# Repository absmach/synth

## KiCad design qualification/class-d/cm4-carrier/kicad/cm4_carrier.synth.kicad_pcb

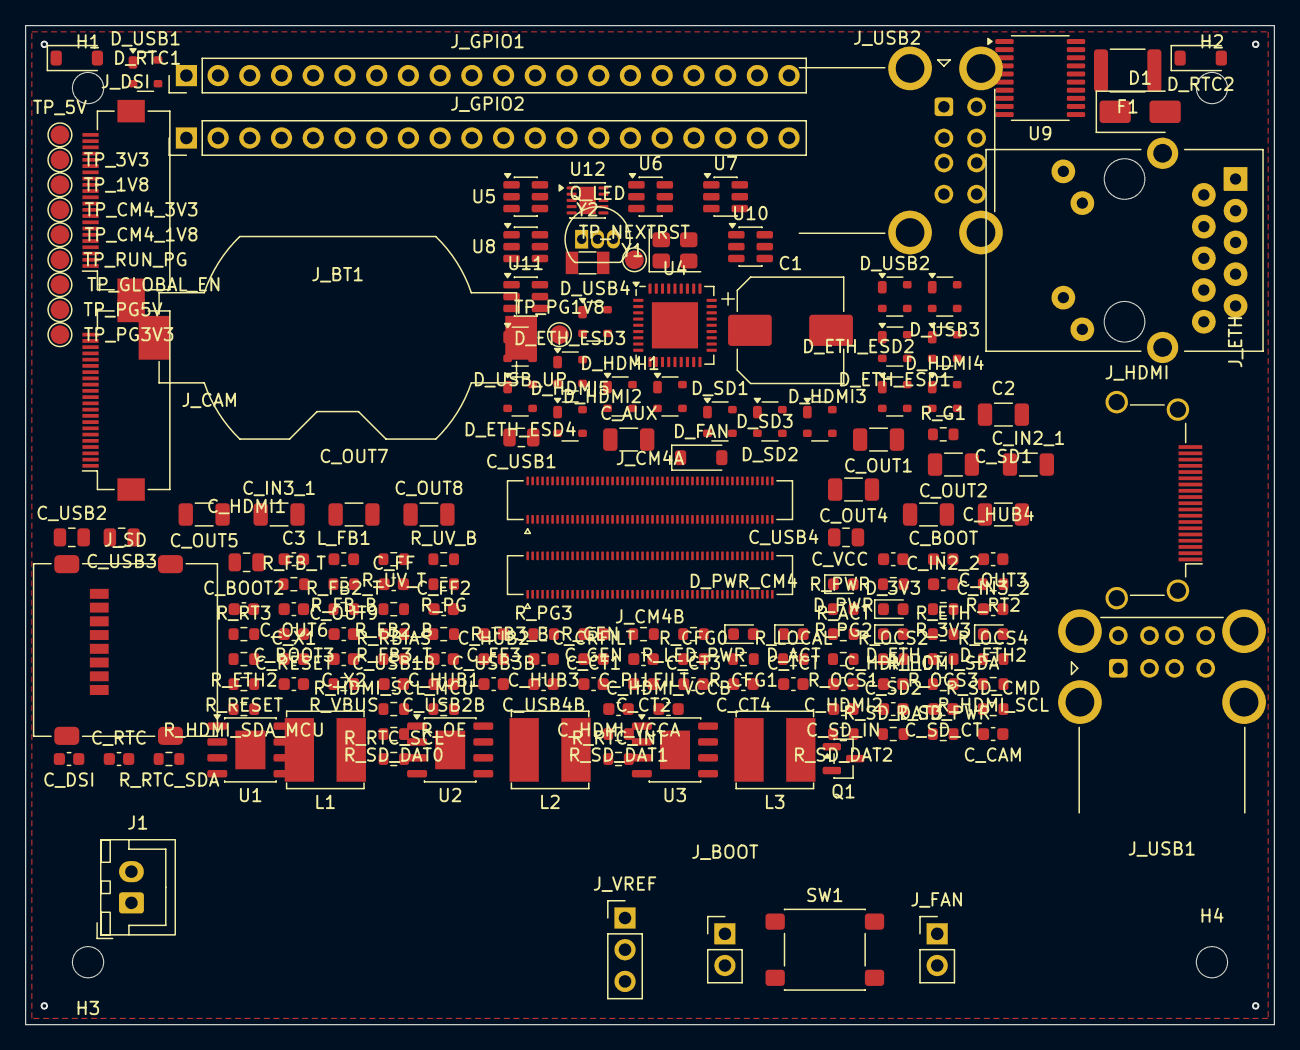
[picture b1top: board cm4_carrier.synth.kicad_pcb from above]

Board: 4 copper layers, 100.0 x 80.0 mm, 184 parts (0 on the bottom side), 158 nets, no tracks yet.

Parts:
C1: 47uF; CP_Elec_8x10
C2: 10uF; C_1206_3216Metric
C3: 220nF; C_0603_1608Metric
C_AUX: 10uF; C_1206_3216Metric
C_BOOT, C_BOOT2, C_BOOT3: 100nF; C_0603_1608Metric
C_CAM: 100nF; C_0603_1608Metric
C_CRFILT: 100nF; C_0603_1608Metric
C_CT1, C_CT2, C_CT3, C_CT4: 1nF; C_0603_1608Metric
C_DSI: 100nF; C_0603_1608Metric
C_FF, C_FF3: 100pF; C_0603_1608Metric
C_FF2: 56pF; C_0603_1608Metric
C_GEN: 100nF; C_0603_1608Metric
C_HDMI1: 1uF; C_0805_2012Metric
C_HDMI2: 100nF; C_0603_1608Metric
C_HDMI_CT: 1nF; C_0603_1608Metric
C_HDMI_VCCA: 100nF; C_0603_1608Metric
C_HDMI_VCCB: 100nF; C_0603_1608Metric
C_HUB1, C_HUB2, C_HUB3: 100nF; C_0603_1608Metric
C_HUB4: 10uF; C_1206_3216Metric
C_IN2_1, C_IN3_1: 10uF; C_1206_3216Metric
C_IN2_2, C_IN3_2: 220nF; C_0603_1608Metric
C_OUT1, C_OUT2, C_OUT4, C_OUT5, C_OUT7, C_OUT8: 22uF; C_1206_3216Metric
C_OUT3, C_OUT6, C_OUT9: 100nF; C_0603_1608Metric
C_PLLFILT: 100nF; C_0603_1608Metric
C_RESET: 1uF; C_0603_1608Metric
C_RTC: 100nF; C_0603_1608Metric
C_SD1: 10uF; C_1206_3216Metric
C_SD2: 100nF; C_0603_1608Metric
C_SD_CT: 1nF; C_0603_1608Metric
C_SD_IN: 100nF; C_0603_1608Metric
C_TCT: 100nF; C_0603_1608Metric
C_USB1, C_USB2, C_USB3, C_USB4: 1uF; C_0805_2012Metric
C_USB1B, C_USB2B, C_USB3B, C_USB4B: 100nF; C_0603_1608Metric
C_VCC: 1uF; C_0603_1608Metric
C_X1, C_X2: 18pF; C_0603_1608Metric
D1: SMAJ15A; D_SMA
D_3V3: 3V3; LED_0603_1608Metric
D_ACT: ACT; LED_0603_1608Metric
D_ETH: ETH_ACT; LED_0603_1608Metric
D_ETH2: ETH_SPD; LED_0603_1608Metric
D_ETH_ESD1, D_ETH_ESD2, D_ETH_ESD3, D_ETH_ESD4: TVS; SOT-143
D_FAN: FLYBACK; D_SOD-123
D_HDMI1, D_HDMI2, D_HDMI3, D_HDMI4, D_HDMI5: TVS; SOT-143
D_PWR: 5V; LED_0603_1608Metric
D_PWR_CM4: PWR; LED_0603_1608Metric
D_RTC1: 3V3; D_SOD-123
D_RTC2: BAT; D_SOD-123
D_SD1, D_SD2, D_SD3: TVS; SOT-143
D_USB1, D_USB2, D_USB3, D_USB4: TVS; SOT-143
D_USB_UP: TVS; SOT-143
F1: 2.6A_PTC; Fuse_1812_4532Metric
H1, H2, H3, H4: M2.5; MountingHole_2.5mm
J1: 12V_IN; JST_XH_B2B-XH-A_1x02_P2.50mm_Vertical
J_BOOT: nRPIBOOT; PinHeader_1x02_P2.54mm_Vertical
J_BT1: CR2032; BatteryHolder_Keystone_1058_1x2032
J_CAM: CSI0; Hirose_FH12-22S-0.5SH_1x22-1MP_P0.50mm_Horizontal
J_CM4A: CM4_A; Hirose_DF40C-100DS-0.4V_2x50_P0.4mm
J_CM4B: CM4_B; Hirose_DF40C-100DS-0.4V_2x50_P0.4mm
J_DSI: DSI0; Hirose_FH12-22S-0.5SH_1x22-1MP_P0.50mm_Horizontal
J_ETH: GbE; RJ45_UDE_RB1-125B8G1A
J_FAN: FAN; PinHeader_1x02_P2.54mm_Vertical
J_GPIO1: GPIO_ODD; PinHeader_1x20_P2.54mm_Vertical
J_GPIO2: GPIO_EVEN; PinHeader_1x20_P2.54mm_Vertical
J_HDMI: HDMI0; HDMI_A_Amphenol_10029449-x01xLF_Horizontal
J_SD: microSD; microSD_HC_Molex_47219-2001
J_USB1: USB1_2; USB_A_CUI_UJ2-ADH-TH_Horizontal_Stacked
J_USB2: USB3_4; USB_A_CUI_UJ2-ADH-TH_Horizontal_Stacked
J_VREF: VREF_SEL; PinHeader_1x03_P2.54mm_Vertical
L1, L2, L3: 6.8uH; L_Bourns_SRN6045TA
L_FB1: 600R; L_0603_1608Metric
Q1: DMP3098L; SOT-23
Q_LED: 2N7000; TO-92_Inline
R_3V3: 470; R_0603_1608Metric
R_ACT: 470; R_0603_1608Metric
R_CFG0, R_CFG1: 10k; R_0603_1608Metric
R_ETH, R_ETH2: 470; R_0603_1608Metric
R_FB2_B: 43.2k; R_0603_1608Metric
R_FB2_T, R_FB3_T: 100k; R_0603_1608Metric
R_FB3_B: 125k; R_0603_1608Metric
R_FB_B: 24.9k; R_0603_1608Metric
R_FB_T: 100k; R_0603_1608Metric
R_G1: 100k; R_0603_1608Metric
R_GEN: 100k; R_0603_1608Metric
R_HDMI_SCL: 2.2k; R_0603_1608Metric
R_HDMI_SCL_MCU: 2.2k; R_0603_1608Metric
R_HDMI_SDA: 2.2k; R_0603_1608Metric
R_HDMI_SDA_MCU: 2.2k; R_0603_1608Metric
R_LED_PWR: 470; R_0603_1608Metric
R_LOCAL: 10k; R_0603_1608Metric
R_OCS1, R_OCS2, R_OCS3, R_OCS4: 10k; R_0603_1608Metric
R_OE: 10k; R_0603_1608Metric
R_PG, R_PG2, R_PG3: 100k; R_0603_1608Metric
R_PWR: 470; R_0603_1608Metric
R_RBIAS: 12k; R_0603_1608Metric
R_RESET: 10k; R_0603_1608Metric
R_RT2, R_RT3: 33k; R_0603_1608Metric
R_RTC_INT: 10k; R_0603_1608Metric
R_RTC_SCL: 10k; R_0603_1608Metric
R_RTC_SDA: 10k; R_0603_1608Metric
R_SD_CMD: 10k; R_0603_1608Metric
R_SD_DAT0, R_SD_DAT1, R_SD_DAT2, R_SD_DAT3: 10k; R_0603_1608Metric
R_SD_PWR: 100k; R_0603_1608Metric
R_UV_B: 10k; R_0603_1608Metric
R_UV_T: 63.4k; R_0603_1608Metric
R_VBUS: 10k; R_0603_1608Metric
SW1: GLOBAL_EN; SW_SPST_PTS645Sx43SMTR92
TP_1V8: 1V8; TestPoint_Pad_D1.5mm
TP_3V3: 3V3; TestPoint_Pad_D1.5mm
TP_5V: 5V; TestPoint_Pad_D1.5mm
TP_CM4_1V8: CM4_1V8; TestPoint_Pad_D1.5mm
TP_CM4_3V3: CM4_3V3; TestPoint_Pad_D1.5mm
TP_GLOBAL_EN: GLOBAL_EN; TestPoint_Pad_D1.5mm
TP_NEXTRST: nEXTRST; TestPoint_Pad_D1.5mm
TP_PG1V8: PG_1V8; TestPoint_Pad_D1.5mm
TP_PG3V3: PG_3V3; TestPoint_Pad_D1.5mm
TP_PG5V: PG_5V; TestPoint_Pad_D1.5mm
TP_RUN_PG: RUN_PG; TestPoint_Pad_D1.5mm
U1: LMR33640; HSOP-8-1EP_3.9x4.9mm_P1.27mm_EP2.41x3.1mm
U2, U3: LMR38010; HSOP-8-1EP_3.9x4.9mm_P1.27mm_EP2.41x3.1mm
U4: USB2514B; QFN-36-1EP_6x6mm_P0.5mm_EP3.7x3.7mm
U5: USB1_PWR; SOT-23-6
U6: USB2_PWR; SOT-23-6
U7: USB3_PWR; SOT-23-6
U8: USB4_PWR; SOT-23-6
U9: TXS0108E; TSSOP-20_4.4x6.5mm_P0.65mm
U10: HDMI_5V; SOT-23-6
U11: SD_PWR; SOT-23-6
U12: PCF85063A; DFN-10-1EP_2.6x2.6mm_P0.5mm_EP1.3x2.2mm
Y1: 24MHz; Crystal_SMD_3225-4Pin_3.2x2.5mm
Y2: 32.768kHz; Crystal_SMD_3215-2Pin_3.2x1.5mm

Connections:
+1V8: C_OUT7.1, C_OUT8.1, C_OUT9.1, J_VREF.3, L3.2, R_FB3_T.1, R_PG3.1, TP_1V8.1
+3V3: C_CAM.1, C_DSI.1, C_HDMI_VCCA.1, C_HUB1.1, C_HUB2.1, C_HUB3.1, C_HUB4.1, C_OUT4.1, C_OUT5.1, C_OUT6.1, C_SD_IN.1, D_ETH_ESD1.4, D_ETH_ESD2.4, D_ETH_ESD3.4, D_ETH_ESD4.4, D_HDMI1.4, D_HDMI2.4, D_HDMI3.4, D_HDMI4.4, D_RTC1.2, D_USB_UP.4, J_CAM.18, J_CAM.22, J_DSI.17, J_DSI.22, J_GPIO1.1, J_GPIO1.9, J_VREF.1, L2.2, R_3V3.1, R_ACT.1, R_ETH.1, R_ETH2.1, R_FB2_T.1, R_GEN.1, R_HDMI_SCL_MCU.1, R_HDMI_SDA_MCU.1, R_LED_PWR.1, R_OCS1.1, R_OCS2.1, R_OCS3.1, R_OCS4.1, R_OE.1, R_PG2.1, R_RESET.1, R_SD_PWR.1, R_VBUS.1, TP_3V3.1, U4.5, U4.10, U4.15, U4.23, U4.29, U4.36, U9.2, U10.3, U11.1
+5V: C_HDMI_VCCB.1, C_OUT1.1, C_OUT2.1, C_OUT3.1, D_FAN.1, D_HDMI5.4, J_CM4A.77, J_CM4A.79, J_CM4A.81, J_CM4A.83, J_CM4A.85, J_CM4A.87, J_FAN.1, J_GPIO2.1, J_GPIO2.2, L1.2, L_FB1.1, R_FB_T.1, R_PG.1, R_PWR.1, TP_5V.1, U5.1, U6.1, U7.1, U8.1, U9.19, U10.1
+5V_AUX: C_AUX.1, C_IN2_1.1, C_IN2_2.1, C_IN3_1.1, C_IN3_2.1, L_FB1.2, U2.3, U3.3
BOOT_1V8: C_BOOT3.1, U3.7
BOOT_3V3: C_BOOT2.1, U2.7
BOOT_5V: C_BOOT.1, U1.7
CAM_CK_N: J_CAM.8, J_CM4B.40
CAM_CK_P: J_CAM.9, J_CM4B.42
CAM_D0_N: J_CAM.2, J_CM4B.28
CAM_D0_P: J_CAM.3, J_CM4B.30
CAM_D1_N: J_CAM.5, J_CM4B.34
CAM_D1_P: J_CAM.6, J_CM4B.36
CAM_GPIO: J_CAM.17, J_CM4A.97
CM4_1V8: J_CM4A.88, J_CM4A.90, TP_CM4_1V8.1
CM4_3V3: J_CM4A.84, J_CM4A.86, TP_CM4_3V3.1
DSI_CK_N: J_CM4B.69, J_DSI.8
DSI_CK_P: J_CM4B.71, J_DSI.9
DSI_D0_N: J_CM4B.57, J_DSI.2
DSI_D0_P: J_CM4B.59, J_DSI.3
DSI_D1_N: J_CM4B.63, J_DSI.5
DSI_D1_P: J_CM4B.65, J_DSI.6
ETH0_N: D_ETH_ESD1.3, J_CM4A.10, J_ETH.R3
ETH0_P: D_ETH_ESD1.2, J_CM4A.12, J_ETH.R2
ETH1_N: D_ETH_ESD2.3, J_CM4A.6, J_ETH.R5
ETH1_P: D_ETH_ESD2.2, J_CM4A.4, J_ETH.R4
ETH2_N: D_ETH_ESD3.3, J_CM4A.9, J_ETH.R7
ETH2_P: D_ETH_ESD3.2, J_CM4A.11, J_ETH.R6
ETH3_N: D_ETH_ESD4.3, J_CM4A.5, J_ETH.R9
ETH3_P: D_ETH_ESD4.2, J_CM4A.3, J_ETH.R8
ETH_LED_ACT: D_ETH.1, J_CM4A.15
ETH_LED_SPD: D_ETH2.1, J_CM4A.17
ETH_TCT: C_TCT.1, J_ETH.R1
FB_1V8: C_FF3.1, R_FB3_B.1, R_FB3_T.2, U3.5
FB_3V3: C_FF2.1, R_FB2_B.1, R_FB2_T.2, U2.5
FB_5V: C_FF.1, R_FB_B.1, R_FB_T.2, U1.5
GLOBAL_EN: C_GEN.1, J_CM4A.99, R_GEN.2, SW1.1, TP_GLOBAL_EN.1
GND: C1.2, C2.2, C3.2, C_AUX.2, C_CAM.2, C_CRFILT.2, C_CT1.2, C_CT2.2, C_CT3.2, C_CT4.2, C_DSI.2, C_GEN.2, C_HDMI1.2, C_HDMI2.2, C_HDMI_CT.2, C_HDMI_VCCA.2, C_HDMI_VCCB.2, C_HUB1.2, C_HUB2.2, C_HUB3.2, C_HUB4.2, C_IN2_1.2, C_IN2_2.2, C_IN3_1.2, C_IN3_2.2, C_OUT1.2, C_OUT2.2, C_OUT3.2, C_OUT4.2, C_OUT5.2, C_OUT6.2, C_OUT7.2, C_OUT8.2, C_OUT9.2, C_PLLFILT.2, C_RESET.2, C_RTC.2, C_SD1.2, C_SD2.2, C_SD_CT.2, C_SD_IN.2, C_TCT.2, C_USB1.2, C_USB1B.2, C_USB2.2, C_USB2B.2, C_USB3.2, C_USB3B.2, C_USB4.2, C_USB4B.2, C_VCC.2, C_X1.2, C_X2.2, D1.2, D_3V3.1, D_ETH_ESD1.1, D_ETH_ESD2.1, D_ETH_ESD3.1, D_ETH_ESD4.1, D_FAN.2, D_HDMI1.1, D_HDMI2.1, D_HDMI3.1, D_HDMI4.1, D_HDMI5.1, D_PWR.1, D_SD1.1, D_SD2.1, D_SD3.1, D_USB1.1, D_USB2.1, D_USB3.1, D_USB4.1, D_USB_UP.1, J1.2, J_BOOT.2, J_BT1.2, J_CAM.1, J_CAM.4, J_CAM.7, J_CAM.10, J_CAM.13, J_CAM.16, J_CAM.19, J_CAM.MP, J_CM4A.1, J_CM4A.2, J_CM4A.7, J_CM4A.8, J_CM4A.13, J_CM4A.14, J_CM4A.22, J_CM4A.23, J_CM4A.32, J_CM4A.33, J_CM4A.42, J_CM4A.43, J_CM4A.52, J_CM4A.53, J_CM4A.59, J_CM4A.60, J_CM4A.65, J_CM4A.66, J_CM4A.71, J_CM4A.74, J_CM4A.98, J_CM4B.1, J_CM4B.7, J_CM4B.8, J_CM4B.13, J_CM4B.14, J_CM4B.19, J_CM4B.20, J_CM4B.25, J_CM4B.26, J_CM4B.31, J_CM4B.32, J_CM4B.37, J_CM4B.38, J_CM4B.44, J_CM4B.50, J_CM4B.55, J_CM4B.56, J_CM4B.61, J_CM4B.62, J_CM4B.67, J_CM4B.68, J_CM4B.73, J_CM4B.74, J_CM4B.79, J_CM4B.80, J_CM4B.85, J_CM4B.86, J_CM4B.91, J_CM4B.92, J_CM4B.97, J_CM4B.98, J_DSI.1, J_DSI.4, J_DSI.7, J_DSI.10, J_DSI.13, J_DSI.16, J_DSI.19, J_DSI.MP, J_ETH.R10, J_ETH.SH, J_FAN.2, J_GPIO1.5, J_GPIO1.13, J_GPIO1.20, J_GPIO2.3, J_GPIO2.7, J_GPIO2.10, J_GPIO2.15, J_GPIO2.17, J_HDMI.2, J_HDMI.5, J_HDMI.8, J_HDMI.11, J_HDMI.17, J_HDMI.SH, J_SD.6, J_SD.SH, J_USB1.4, J_USB1.8, J_USB1.SH, J_USB2.4, J_USB2.8, J_USB2.SH, Q_LED.1, R_3V3.2, R_CFG0.2, R_CFG1.2, R_FB2_B.2, R_FB3_B.2, R_FB_B.2, R_LOCAL.2, R_PWR.2, R_RBIAS.2, R_RT2.2, R_RT3.2, R_UV_B.2, SW1.2, U1.1, U1.9, U2.1, U2.9, U3.1, U3.9, U4.37, U5.2, U6.2, U7.2, U8.2, U9.11, U10.2, U11.2, U12.5, U12.11, Y1.2, Y1.4
GPIO2: J_CM4A.58, J_GPIO1.2
GPIO3: J_CM4A.56, J_GPIO1.3
GPIO4: J_CM4A.54, J_GPIO1.4
GPIO5: J_CM4A.34, J_GPIO1.15
GPIO6: J_CM4A.30, J_GPIO1.16
GPIO7: J_CM4A.37, J_GPIO2.13
GPIO8: J_CM4A.39, J_GPIO2.12
GPIO9: J_CM4A.40, J_GPIO1.11
GPIO10: J_CM4A.44, J_GPIO1.10
GPIO11: J_CM4A.38, J_GPIO1.12
GPIO12: J_CM4A.31, J_GPIO2.16
GPIO13: J_CM4A.28, J_GPIO1.17
GPIO14: J_CM4A.55, J_GPIO2.4
GPIO15: J_CM4A.51, J_GPIO2.5
GPIO16: J_CM4A.29, J_GPIO2.18
GPIO17: J_CM4A.50, J_GPIO1.6
GPIO18: J_CM4A.49, J_GPIO2.6
GPIO19: J_CM4A.26, J_GPIO1.18
GPIO20: J_CM4A.27, J_GPIO2.19
GPIO21: J_CM4A.25, J_GPIO2.20
GPIO22: J_CM4A.46, J_GPIO1.8
GPIO23: J_CM4A.47, J_GPIO2.8
GPIO24: J_CM4A.45, J_GPIO2.9
GPIO25: J_CM4A.41, J_GPIO2.11
GPIO26: J_CM4A.24, J_GPIO1.19, R_RTC_INT.2, U12.4
GPIO27: J_CM4A.48, J_GPIO1.7
GPIO_VREF: J_CM4A.78, J_VREF.2
HDMI_5V: C_HDMI1.1, C_HDMI2.1, J_HDMI.18, U10.6
HDMI_CEC: J_CM4B.51, J_HDMI.13
HDMI_CK_N: D_HDMI4.3, J_CM4B.90, J_HDMI.12
HDMI_CK_P: D_HDMI4.2, J_CM4B.88, J_HDMI.10
HDMI_CT: C_HDMI_CT.1, U10.4
HDMI_D0_N: D_HDMI3.3, J_CM4B.84, J_HDMI.9
HDMI_D0_P: D_HDMI3.2, J_CM4B.82, J_HDMI.7
HDMI_D1_N: D_HDMI2.3, J_CM4B.78, J_HDMI.6
HDMI_D1_P: D_HDMI2.2, J_CM4B.76, J_HDMI.4
HDMI_D2_N: D_HDMI1.3, J_CM4B.72, J_HDMI.3
HDMI_D2_P: D_HDMI1.2, J_CM4B.70, J_HDMI.1
HDMI_HPD: J_CM4B.53, J_HDMI.19
HDMI_OE: R_OE.2, U9.10
HDMI_SCL_CONN: D_HDMI5.3, J_HDMI.15, R_HDMI_SCL.1, U9.18
HDMI_SCL_MCU: J_CM4B.100, R_HDMI_SCL_MCU.2, U9.3
HDMI_SDA_CONN: D_HDMI5.2, J_HDMI.16, R_HDMI_SDA.1, U9.20
HDMI_SDA_MCU: J_CM4B.99, R_HDMI_SDA_MCU.2, U9.1
HUB_CFG0: R_CFG0.1, U4.24
HUB_CFG1: R_CFG1.1, U4.25
HUB_CRFILT: C_CRFILT.1, U4.14
HUB_LOCAL: R_LOCAL.1, U4.28
HUB_OCS1: R_OCS1.2, U4.13
HUB_OCS2: R_OCS2.2, U4.17
HUB_OCS3: R_OCS3.2, U4.19
HUB_OCS4: R_OCS4.2, U4.21
HUB_PLLFILT: C_PLLFILT.1, U4.34
HUB_RBIAS: R_RBIAS.1, U4.35
HUB_RESET: C_RESET.1, R_RESET.2, U4.26
HUB_VBUS_DET: R_VBUS.2, U4.27
HUB_XTAL1: C_X1.1, U4.33, Y1.1
HUB_XTAL2: C_X2.1, U4.32, Y1.3
ID_SC: J_CM4A.35, J_GPIO2.14
ID_SD: J_CM4A.36, J_GPIO1.14
LED_ACT_A: D_ACT.2, R_ACT.2
LED_ETH2_A: D_ETH2.2, R_ETH2.2
LED_ETH_A: D_ETH.2, R_ETH.2
LED_PWR_CM4: D_PWR_CM4.1, Q_LED.3
LED_PWR_CM4_A: D_PWR_CM4.2, R_LED_PWR.2
NEXTRST: J_CM4A.100, TP_NEXTRST.1
NRPIBOOT: J_BOOT.1, J_CM4A.93
PG_1V8: R_PG3.2, TP_PG1V8.1, U3.6
PG_3V3: R_PG2.2, TP_PG3V3.1, U2.6, U3.2
PG_5V: R_PG.2, TP_PG5V.1, U1.4, U2.2
PI_LED_ACT: D_ACT.1, J_CM4A.21
PI_LED_NPWR: J_CM4A.95, Q_LED.2
RTC_BAT: D_RTC2.2, J_BT1.1
RTC_OSC1: U12.1, Y2.1
RTC_OSC2: U12.2, Y2.2
RTC_VDD: C_RTC.1, D_RTC1.1, D_RTC2.1, R_RTC_INT.1, R_RTC_SCL.1, R_RTC_SDA.1, U12.3, U12.10
RT_1V8: R_RT3.1, U3.4
RT_3V3: R_RT2.1, U2.4
RUN_PG: J_CM4A.92, TP_RUN_PG.1
SCL0: J_CAM.20, J_CM4A.80, J_DSI.20, R_RTC_SCL.2, U12.7
SDA0: J_CAM.21, J_CM4A.82, J_DSI.21, R_RTC_SDA.2, U12.6
SD_CLK: D_SD1.2, J_CM4A.57, J_SD.5
SD_CMD: D_SD1.3, J_CM4A.62, J_SD.3, R_SD_CMD.2
SD_CT: C_SD_CT.1, U11.4
SD_DAT0: D_SD2.2, J_CM4A.63, J_SD.7, R_SD_DAT0.2
SD_DAT1: D_SD2.3, J_CM4A.67, J_SD.8, R_SD_DAT1.2
SD_DAT2: D_SD3.2, J_CM4A.69, J_SD.1, R_SD_DAT2.2
SD_DAT3: D_SD3.3, J_CM4A.61, J_SD.2, R_SD_DAT3.2
SD_PWR_ON: J_CM4A.75, R_SD_PWR.2, U11.3
SD_VDD: C_SD1.1, C_SD2.1, D_SD1.4, D_SD2.4, D_SD3.4, J_SD.4, R_SD_CMD.1, R_SD_DAT0.1, R_SD_DAT1.1, R_SD_DAT2.1, R_SD_DAT3.1, U11.6
SW_1V8: C_BOOT3.2, L3.1, U3.8
SW_3V3: C_BOOT2.2, L2.1, U2.8
SW_5V: C_BOOT.2, L1.1, U1.8
USB1_N: D_USB1.3, J_USB1.2, U4.1
USB1_P: D_USB1.2, J_USB1.3, U4.2
USB2_N: D_USB2.3, J_USB1.6, U4.3
USB2_P: D_USB2.2, J_USB1.7, U4.4
USB3_N: D_USB3.3, J_USB2.2, U4.6
USB3_P: D_USB3.2, J_USB2.3, U4.7
USB4_N: D_USB4.3, J_USB2.6, U4.8
USB4_P: D_USB4.2, J_USB2.7, U4.9
USB_CT1: C_CT1.1, U5.4
USB_CT2: C_CT2.1, U6.4
USB_CT3: C_CT3.1, U7.4
USB_CT4: C_CT4.1, U8.4
USB_ON1: U4.12, U5.3
USB_ON2: U4.16, U6.3
USB_ON3: U4.18, U7.3
USB_ON4: U4.20, U8.3
USB_UP_N: D_USB_UP.3, J_CM4B.3, U4.30
USB_UP_P: D_USB_UP.2, J_CM4B.5, U4.31
USB_VBUS1: C_USB1.1, C_USB1B.1, D_USB1.4, J_USB1.1, U5.6
USB_VBUS2: C_USB2.1, C_USB2B.1, D_USB2.4, J_USB1.5, U6.6
USB_VBUS3: C_USB3.1, C_USB3B.1, D_USB3.4, J_USB2.1, U7.6
USB_VBUS4: C_USB4.1, C_USB4B.1, D_USB4.4, J_USB2.5, U8.6
VCC_5V: C_VCC.1, U1.6
VIN_12V: F1.1, J1.1
VIN_FUSED: F1.2, Q1.2
VIN_GATE: Q1.1, R_G1.2
VIN_PROT: C1.1, C2.1, C3.1, D1.1, Q1.3, R_G1.1, R_UV_T.1, U1.2

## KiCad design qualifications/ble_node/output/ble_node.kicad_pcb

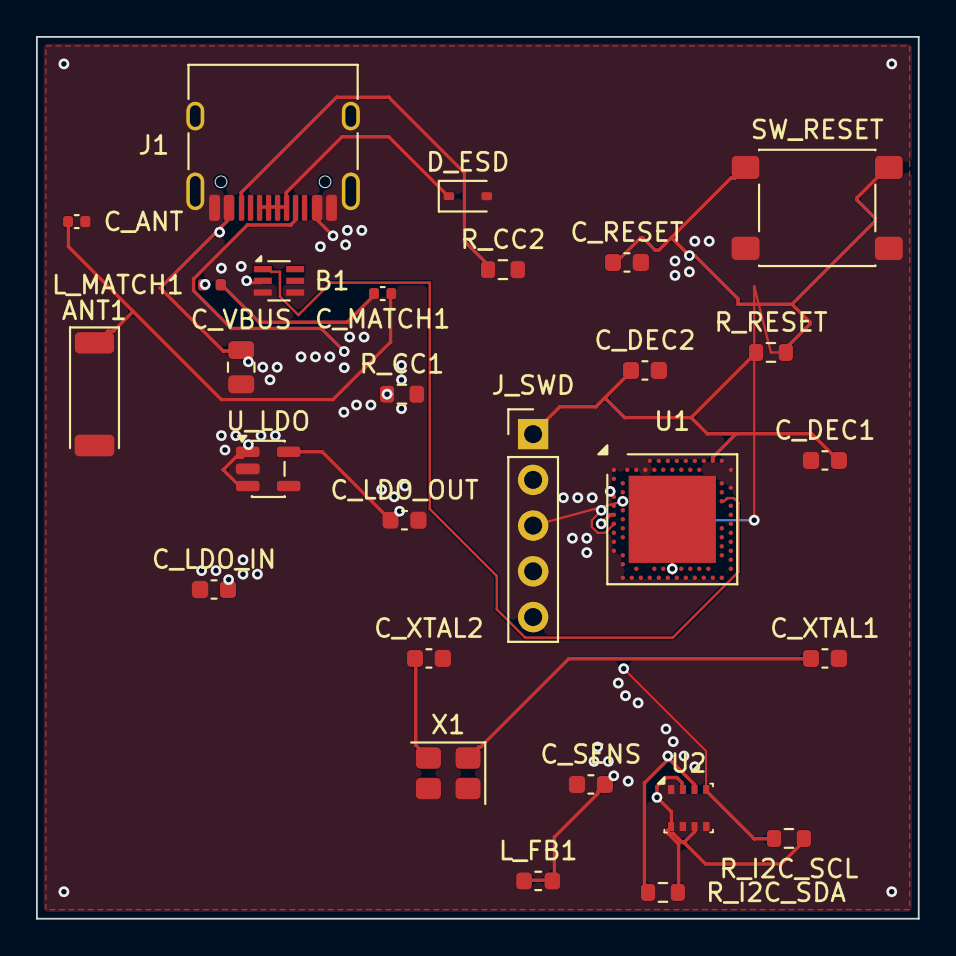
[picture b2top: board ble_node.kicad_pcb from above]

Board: 4 copper layers, 49.0 x 49.0 mm, 28 parts (0 on the bottom side), 17 nets.

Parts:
ANT1: 2.4GHz Chip Ant; Johanson_2450AT43F0100
B1: 2.4GHz Balun; Balun_Johanson_0896BM15A0001
C_ANT: 1.0pF; C_0402_1005Metric
C_DEC1, C_DEC2: 100nF; C_0603_1608Metric
C_LDO_IN: 1uF; C_0603_1608Metric
C_LDO_OUT: 1uF; C_0603_1608Metric
C_MATCH1: 1.0pF; C_0402_1005Metric
C_RESET: 100nF; C_0603_1608Metric
C_SENS: 100nF; C_0603_1608Metric
C_VBUS: 10uF; C_0805_2012Metric
C_XTAL1, C_XTAL2: 12pF; C_0603_1608Metric
D_ESD: (no value); D_SOD-323
J1: TYPE-C-31-M-12; USB_C_Receptacle_HRO_TYPE-C-31-M-12
J_SWD: SWD Header; PinHeader_1x05_P2.54mm_Vertical
L_FB1: (no value); L_0603_1608Metric
L_MATCH1: 3.9nH; L_0402_1005Metric
R_CC1, R_CC2: 5.1k; R_0603_1608Metric
R_I2C_SCL, R_I2C_SDA: 4.7k; R_0603_1608Metric
R_RESET: 10k; R_0603_1608Metric
SW_RESET: (no value); SW_SPST_PTS645Sx43SMTR92
U1: nRF52840-QIAA; Nordic_AQFN-73-1EP_7x7mm_P0.5mm
U2: BME680; Bosch_LGA-8_2.5x2.5mm_P0.65mm_ClockwisePinNumbering
U_LDO: LP5907-3.3; SOT-23-5
X1: 32 MHz; Crystal_SMD_3225-4Pin_3.2x2.5mm

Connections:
+3V3: C_DEC1.1, C_DEC2.1, C_LDO_OUT.1, C_SENS.1, J_SWD.1, L_FB1.1, L_FB1.2, R_I2C_SCL.2, R_I2C_SDA.2, R_RESET.1, U1.A22, U2.2, U2.6, U2.8, U_LDO.5
ANT_FEED: B1.1, U1.H23
GND: ANT1.2, B1.3, B1.4, C_ANT.2, C_DEC1.2, C_DEC2.2, C_LDO_IN.2, C_LDO_OUT.2, C_RESET.2, C_SENS.2, C_VBUS.2, C_XTAL1.2, C_XTAL2.2, D_ESD.2, J1.A1, J1.A12, J1.B1, J1.B12, J1.SH, J_SWD.4, R_CC1.2, R_CC2.2, SW_RESET.2, U1.B7, U2.1, U2.5, U2.7, U_LDO.2
net_0: C_LDO_IN.1, C_VBUS.1, J1.A4, J1.A9, J1.B4, J1.B9, U_LDO.1, U_LDO.3
net_3: J1.A5, R_CC1.1
net_4: J1.B5, R_CC2.1
net_5: D_ESD.1, J1.A6, J1.A7, J1.B6, J1.B7
net_6: C_RESET.1, J_SWD.5, R_RESET.2, SW_RESET.1, U1.AC13
net_7: C_XTAL1.1, X1.1
net_8: C_XTAL2.1, X1.2
net_9: B1.2, L_MATCH1.1
net_10: C_MATCH1.1, L_MATCH1.2
net_11: ANT1.1, C_ANT.1, C_MATCH1.2
net_12: R_I2C_SDA.1, U1.L1, U2.3
net_13: R_I2C_SCL.1, U1.N1, U2.4
net_14: J_SWD.2, U1.G1
net_15: J_SWD.3, U1.H2

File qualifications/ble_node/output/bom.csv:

refdes,value,kind,description,kicad_symbol,kicad_footprint,lcsc_pn,mpn
ANT1,2.4GHz Chip Ant,antenna,"Ceramic chip antenna, 2.4 GHz, 1 dBi, SMD",Device:Antenna_Chip,RF_Antenna:Johanson_2450AT43F0100,C17192881,2450AT43F0100E
B1,2.4GHz Balun,filter,"2.4 GHz balun + matching network, integrated SMD",RF_Module:balun_2g4,RF_Converter:Balun_Johanson_0896BM15A0001,,2450BL15B100
C_ANT,1.0pF,capacitor,"Generic 0402 MLCC, X7R/X5R, any value",Device:C,Capacitor_SMD:C_0402_1005Metric,,
C_DEC1,100nF,capacitor,"Generic 0603 MLCC, X7R/X5R, any value",Device:C,Capacitor_SMD:C_0603_1608Metric,,
C_DEC2,100nF,capacitor,"Generic 0603 MLCC, X7R/X5R, any value",Device:C,Capacitor_SMD:C_0603_1608Metric,,
C_LDO_IN,1uF,capacitor,"Generic 0603 MLCC, X7R/X5R, any value",Device:C,Capacitor_SMD:C_0603_1608Metric,,
C_LDO_OUT,1uF,capacitor,"Generic 0603 MLCC, X7R/X5R, any value",Device:C,Capacitor_SMD:C_0603_1608Metric,,
C_MATCH1,1.0pF,capacitor,"Generic 0402 MLCC, X7R/X5R, any value",Device:C,Capacitor_SMD:C_0402_1005Metric,,
C_RESET,100nF,capacitor,"Generic 0603 MLCC, X7R/X5R, any value",Device:C,Capacitor_SMD:C_0603_1608Metric,,
C_SENS,100nF,capacitor,"Generic 0603 MLCC, X7R/X5R, any value",Device:C,Capacitor_SMD:C_0603_1608Metric,,
C_VBUS,10uF,capacitor,"Generic 0805 MLCC, X7R/X5R, any value",Device:C,Capacitor_SMD:C_0805_2012Metric,,
C_XTAL1,12pF,capacitor,"Generic 0603 MLCC, X7R/X5R, any value",Device:C,Capacitor_SMD:C_0603_1608Metric,,
C_XTAL2,12pF,capacitor,"Generic 0603 MLCC, X7R/X5R, any value",Device:C,Capacitor_SMD:C_0603_1608Metric,,
D_ESD,(no value),diode,"USB-line ESD protection (TVS diode array), bidirectional",Device:D_TVS,Diode_SMD:D_SOD-323,,
J1,TYPE-C-31-M-12,connector,"USB-C receptacle, 24-pin SMD. Modelled here with primary and mirrored power/ground/data pins for full pad coverage.",Connector:USB_C_Receptacle,Connector_USB:USB_C_Receptacle_HRO_TYPE-C-31-M-12,C165948,TYPE-C-31-M-12
J_SWD,SWD Header,connector,"1x5 through-hole pin header, 2.54 mm pitch (SWD); datasheet_url is the product page of the Harwin M20 series, no manufacturer PDF link was verifiable",Connector_Generic:Conn_01x05,Connector_PinHeader_2.54mm:PinHeader_1x05_P2.54mm_Vertical,,
L_FB1,(no value),inductor,"0603 ferrite bead, 600Ω @ 100MHz — EMI suppression",Device:Ferrite_Bead,Inductor_SMD:L_0603_1608Metric,,
L_MATCH1,3.9nH,inductor,"Generic 0402 wirewound inductor, any value",Device:L,Inductor_SMD:L_0402_1005Metric,,
R_CC1,5.1k,resistor,"Generic 0603 thick-film resistor, any value",Device:R_US,Resistor_SMD:R_0603_1608Metric,,
R_CC2,5.1k,resistor,"Generic 0603 thick-film resistor, any value",Device:R_US,Resistor_SMD:R_0603_1608Metric,,
R_I2C_SCL,4.7k,resistor,"Generic 0603 thick-film resistor, any value",Device:R_US,Resistor_SMD:R_0603_1608Metric,,
R_I2C_SDA,4.7k,resistor,"Generic 0603 thick-film resistor, any value",Device:R_US,Resistor_SMD:R_0603_1608Metric,,
R_RESET,10k,resistor,"Generic 0603 thick-film resistor, any value",Device:R_US,Resistor_SMD:R_0603_1608Metric,,
SW_RESET,(no value),switch,Generic SPST tactile button,Switch:SW_Push,Button_Switch_SMD:SW_SPST_PTS645Sx43SMTR92,,
U1,nRF52840-QIAA,mcu,"Nordic nRF52840 ARM Cortex-M4F with BLE 5, I2C-capable GPIO naming",RF_Module:NRF52840-QIAA,Package_DFN_QFN:Nordic_AQFN-73-1EP_7x7mm_P0.5mm,C190794,NRF52840-QIAA-R
U2,BME680,sensor,"Bosch BME680 environmental sensor: T/RH/P/VOC, I²C",Sensor:BME680,Package_LGA:Bosch_LGA-8_2.5x2.5mm_P0.65mm_ClockwisePinNumbering,,
U_LDO,LP5907-3.3,regulator,"TI LP5907 3.3V low-noise LDO, 250mA, SOT-23-5",Regulator_Linear:LP5907MFX-3.3,Package_TO_SOT_SMD:SOT-23-5,C83437,LP5907MFX-3.3
X1,32 MHz,crystal,"Generic quartz crystal, 2-pin SMD",Device:Crystal,Crystal:Crystal_SMD_3225-4Pin_3.2x2.5mm,,

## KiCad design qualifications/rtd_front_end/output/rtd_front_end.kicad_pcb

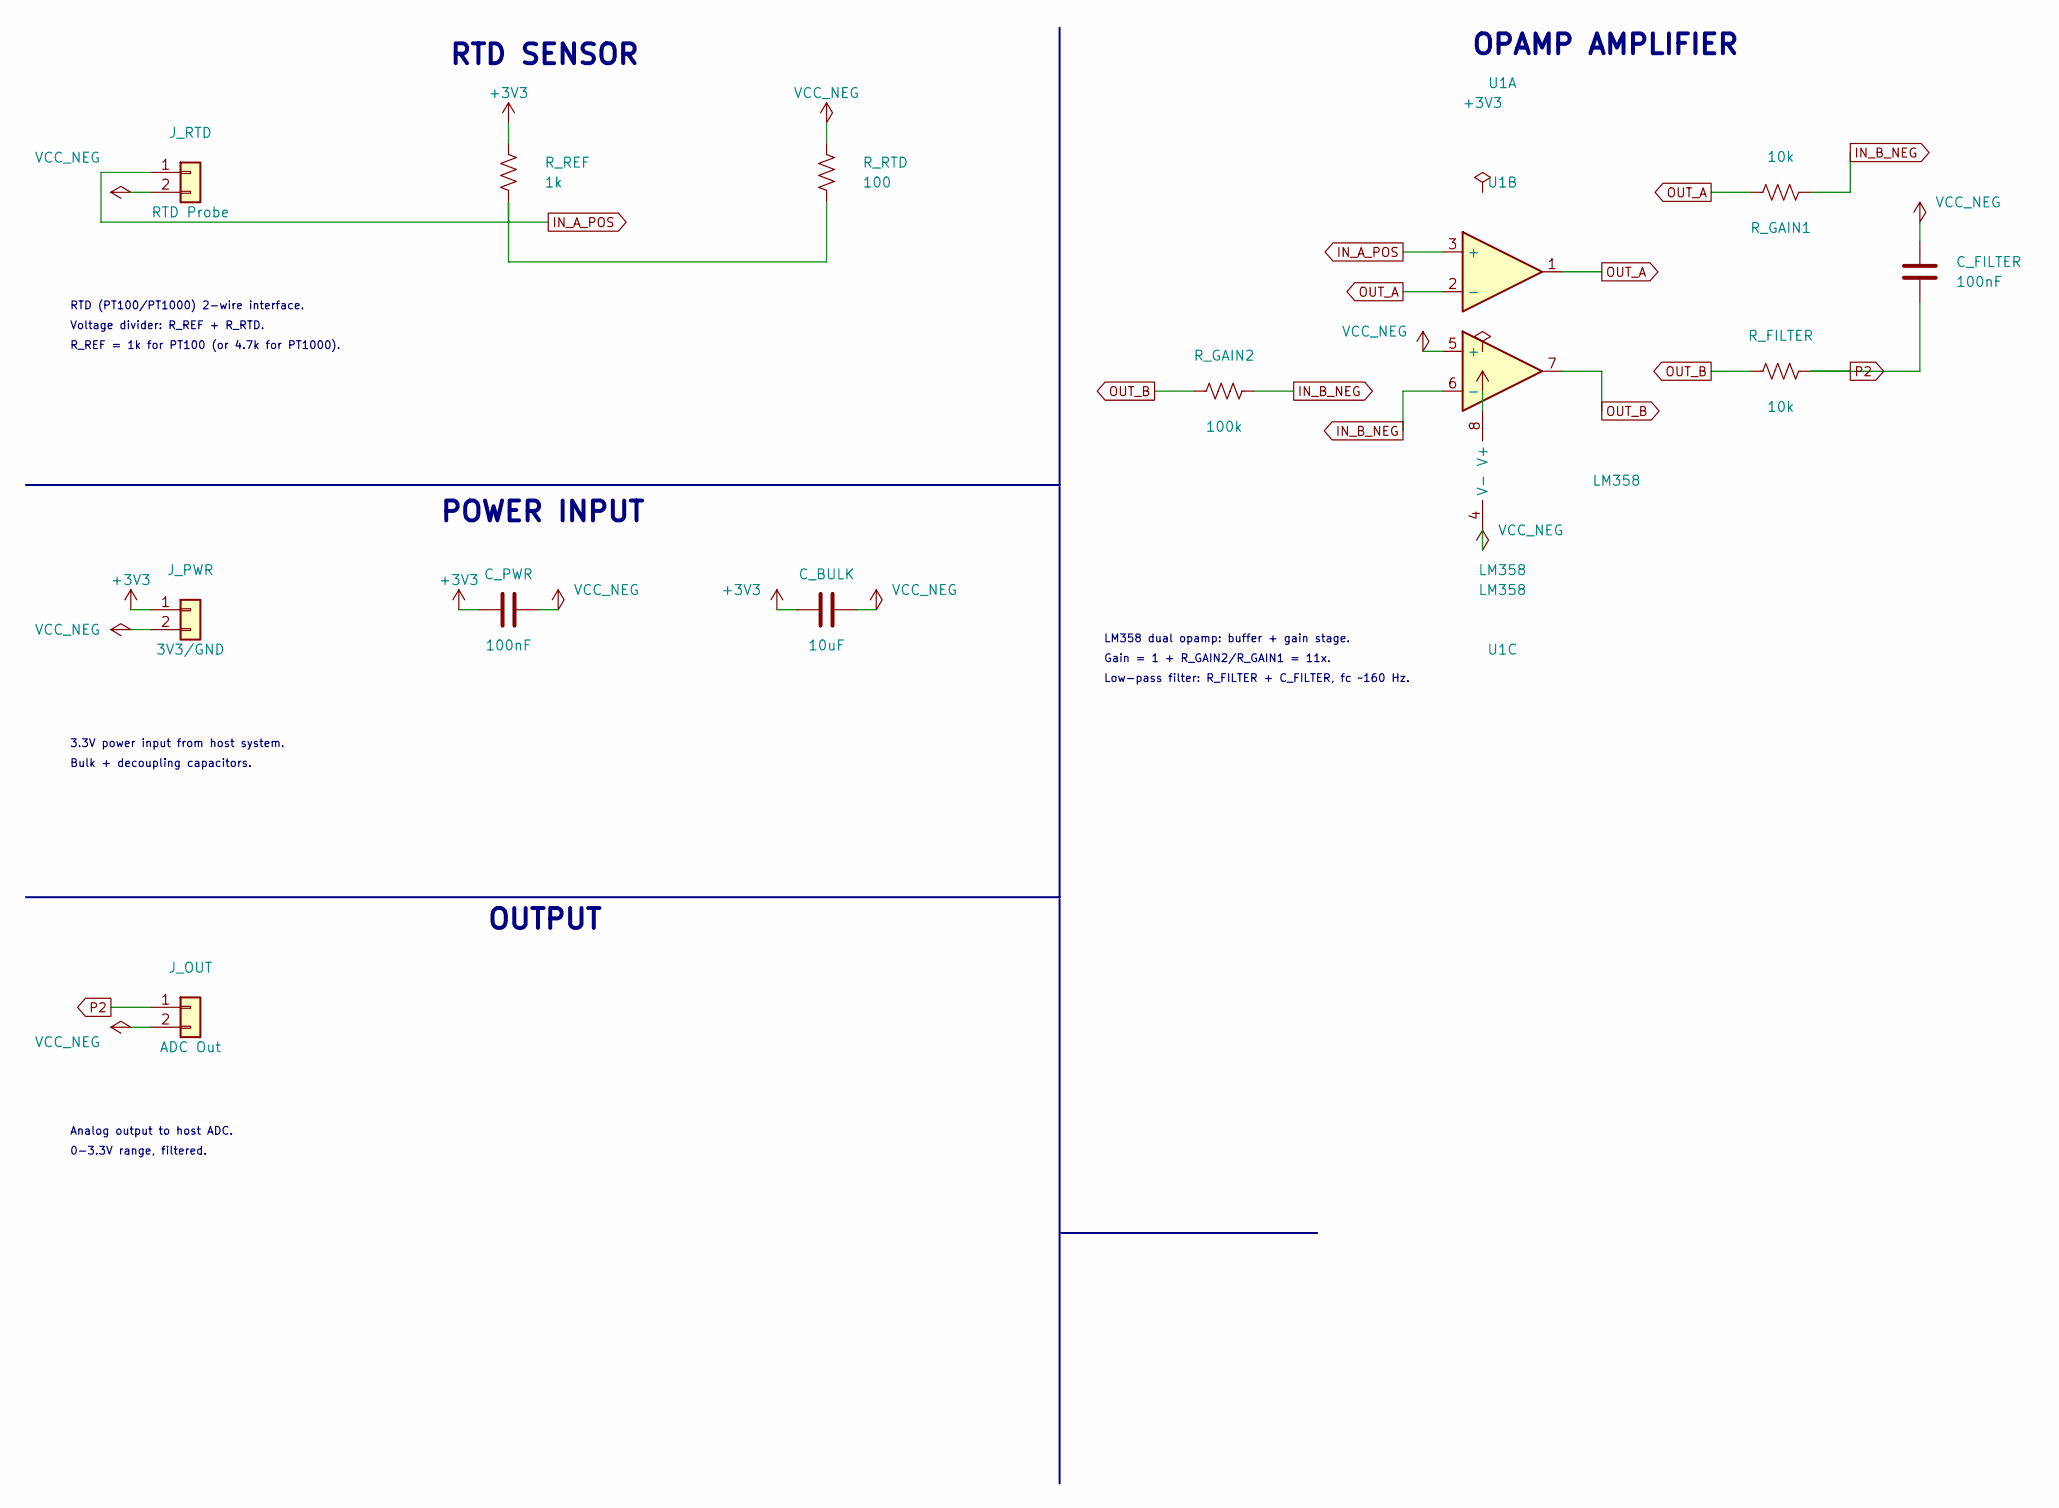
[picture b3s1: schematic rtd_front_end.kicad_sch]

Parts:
C_BULK: 10uF; C_0805_2012Metric
C_FILTER: 100nF; C_0603_1608Metric
C_PWR: 100nF; C_0603_1608Metric
J_OUT: ADC Out; PinHeader_1x02_P2.54mm_Vertical; MPN HX PZ2.54-1x2P ZZ; LCSC C32713268
J_PWR: 3V3/GND; PinHeader_1x02_P2.54mm_Vertical; MPN HX PZ2.54-1x2P ZZ; LCSC C32713268
J_RTD: RTD Probe; PinHeader_1x02_P2.54mm_Vertical; MPN HX PZ2.54-1x2P ZZ; LCSC C32713268
R_FILTER: 10k; R_0603_1608Metric
R_GAIN1: 10k; R_0603_1608Metric
R_GAIN2: 100k; R_0603_1608Metric
R_REF: 1k; R_0603_1608Metric
R_RTD: 100; R_0603_1608Metric
U1: LM358; DIP-8_W7.62mm

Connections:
+3V3: C_BULK.1, C_PWR.1, J_PWR.1, R_REF.1, U1.8 (V+)
GND: C_BULK.2, C_FILTER.2, C_PWR.2, J_OUT.2, J_PWR.2, J_RTD.2, R_RTD.2, U1.4 (V-), U1.5 (+)
net_2: J_RTD.1, R_REF.2, R_RTD.1, U1.3 (+)
net_3: R_GAIN1.1, U1.1, U1.2 (-)
net_4: R_GAIN1.2, R_GAIN2.1, U1.6 (-)
net_5: R_FILTER.1, R_GAIN2.2, U1.7
net_6: C_FILTER.1, J_OUT.1, R_FILTER.2

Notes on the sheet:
POWER INPUT
RTD SENSOR
OPAMP AMPLIFIER
OUTPUT
3.3V power input from host system.
Bulk + decoupling capacitors.
RTD (PT100/PT1000) 2-wire interface.
Voltage divider: R_REF + R_RTD.
R_REF = 1k for PT100 (or 4.7k for PT1000).
LM358 dual opamp: buffer + gain stage.
Gain = 1 + R_GAIN2/R_GAIN1 = 11x.
Low-pass filter: R_FILTER + C_FILTER, fc ~160 Hz.
Analog output to host ADC.
0-3.3V range, filtered.

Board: 2 copper layers, 12 parts (0 on the bottom side), 7 nets, no tracks yet.

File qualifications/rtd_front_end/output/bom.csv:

refdes,value,kind,description,kicad_symbol,kicad_footprint,lcsc_pn,mpn
C_BULK,10uF,capacitor,"Generic 0805 MLCC, X7R/X5R, any value",Device:C,Capacitor_SMD:C_0805_2012Metric,,
C_FILTER,100nF,capacitor,"Generic 0603 MLCC, X7R/X5R, any value",Device:C,Capacitor_SMD:C_0603_1608Metric,,
C_PWR,100nF,capacitor,"Generic 0603 MLCC, X7R/X5R, any value",Device:C,Capacitor_SMD:C_0603_1608Metric,,
J_OUT,ADC Out,connector,"1x2 through-hole pin header, 2.54mm pitch, for a jumper",Connector_Generic:Conn_01x02,Connector_PinHeader_2.54mm:PinHeader_1x02_P2.54mm_Vertical,C32713268,HX PZ2.54-1x2P ZZ
J_PWR,3V3/GND,connector,"1x2 through-hole pin header, 2.54mm pitch, for a jumper",Connector_Generic:Conn_01x02,Connector_PinHeader_2.54mm:PinHeader_1x02_P2.54mm_Vertical,C32713268,HX PZ2.54-1x2P ZZ
J_RTD,RTD Probe,connector,"1x2 through-hole pin header, 2.54mm pitch, for a jumper",Connector_Generic:Conn_01x02,Connector_PinHeader_2.54mm:PinHeader_1x02_P2.54mm_Vertical,C32713268,HX PZ2.54-1x2P ZZ
R_FILTER,10k,resistor,"Generic 0603 thick-film resistor, any value",Device:R_US,Resistor_SMD:R_0603_1608Metric,,
R_GAIN1,10k,resistor,"Generic 0603 thick-film resistor, any value",Device:R_US,Resistor_SMD:R_0603_1608Metric,,
R_GAIN2,100k,resistor,"Generic 0603 thick-film resistor, any value",Device:R_US,Resistor_SMD:R_0603_1608Metric,,
R_REF,1k,resistor,"Generic 0603 thick-film resistor, any value",Device:R_US,Resistor_SMD:R_0603_1608Metric,,
R_RTD,100,resistor,"Generic 0603 thick-film resistor, any value",Device:R_US,Resistor_SMD:R_0603_1608Metric,,
U1,LM358,opamp,"TI LM358 dual op-amp, SOIC-8",Amplifier_Operational:LM358,Package_DIP:DIP-8_W7.62mm,,
